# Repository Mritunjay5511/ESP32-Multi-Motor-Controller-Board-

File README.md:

# ESP32-Multi-Motor-Controller-Board-
Custom ESP32-WROOM-32 robotics controller PCB with onboard buck/LDO power regulation, auto-program circuit, and BTS7960/RMCS/relay/servo interfaces. Designed in KiCad.
# ESP32 Dual BTS7960 Motor Driver Breakout Board

A custom 2-layer PCB designed to handle heavy-duty robotics applications. It acts as a central control board breaking out an ESP32 to interface with dual BTS7960 motor drivers, an RMCS driver, and features onboard power regulation.

## Features
- **Microcontroller:** ESP32-WROOM-32
- **Power Stage:** LM2596 Buck Regulator (12v to 5v switching) & AMS1117-3.3 (5v to 3.3v switching)
- **Motor Control Interfaces:** 2x BTS7960 H-Bridge Drivers, 1x RMCS Driver interface
- **Peripherals:** Integrated Micro USB for programming (CH340C), Boot & Reset tactile switches, and broken-out GPIO headers.

## Design Highlights
- Optimized high-frequency switching loops for the buck regulator to minimize EMI.
- Completely isolated RF antenna keepout zone on both layers for maximum wireless signal integrity.
- Solid ground planes on both layers for optimal return paths.

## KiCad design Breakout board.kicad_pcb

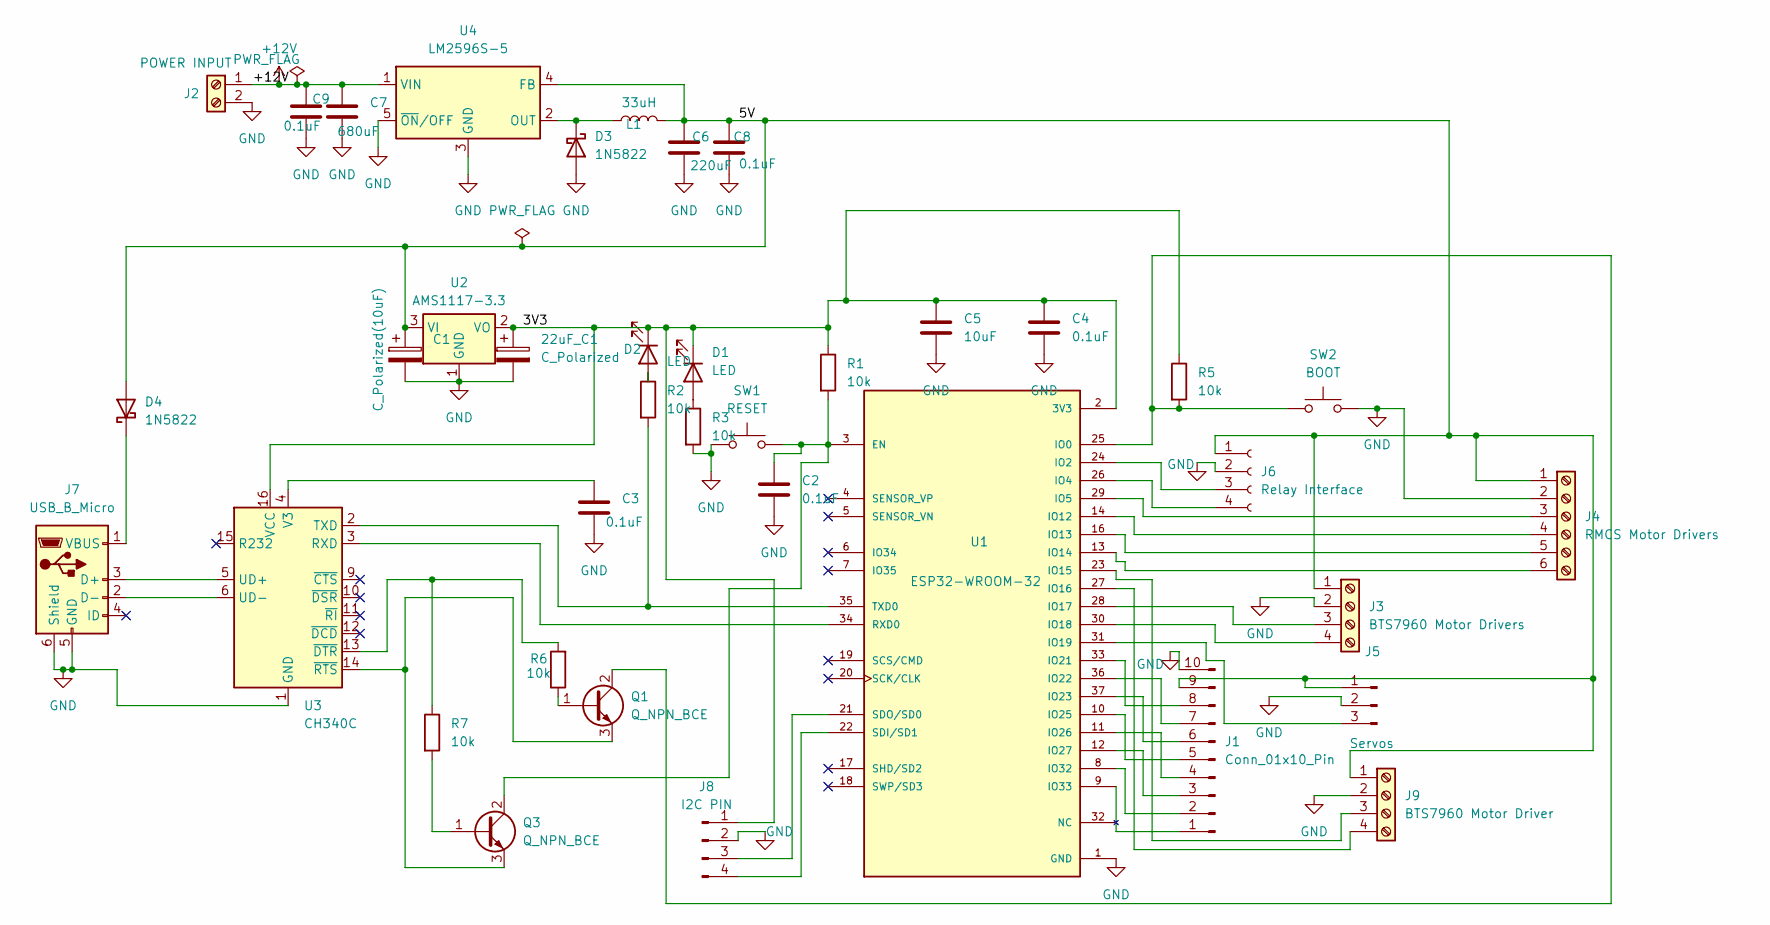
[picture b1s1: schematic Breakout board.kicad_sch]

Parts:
22uF_C1: C_Polarized; CP_Elec_4x5.4
C1: C_Polarized(10uF); CP_Elec_4x5.4
C2, C3, C4, C8, C9: 0.1uF; C_1206_3216Metric
C5: 10uF; C_1206_3216Metric
C6: 220uF; C_1206_3216Metric
C7: 680uF; C_1206_3216Metric
D1, D2: LED; LED_1206_3216Metric
D3: 1N5822; D_DO-201AD_P12.70mm_Horizontal
D4: 1N5822; D_DO-201AD_P15.24mm_Horizontal
J1: Conn_01x10_Pin; PinHeader_1x10_P2.54mm_Vertical
J2: POWER INPUT; TerminalBlock_Phoenix_MKDS-1,5-2-5.08_1x02_P5.08mm_Horizont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
J3: BTS7960 Motor Drivers; TerminalBlock_Phoenix_MKDS-1,5-4-5.08_1x04_P5.08mm_Horizont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
J4: RMCS Motor Drivers; TerminalBlock_Phoenix_MKDS-1,5-6-5.08_1x06_P5.08mm_Horizont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
J5: Servos; PinHeader_1x03_P2.54mm_Vertical
J6: Relay Interface; PinSocket_1x04_P2.54mm_Vertical
J7: USB_B_Micro; USB_Micro-B_Molex-105017-0001
J8: I2C PIN; PinHeader_1x04_P2.54mm_Vertical
J9: BTS7960 Motor Driver; TerminalBlock_Phoenix_MKDS-1,5-4-5.08_1x04_P5.08mm_Horizont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
L1: 33uH; L_1206_3216Metric
Q1, Q3: Q_NPN_BCE; SOT-23
R1, R2, R3, R5, R6, R7: 10k; R_1206_3216Metric
SW1: RESET; SW_PUSH_6mm
SW2: BOOT; SW_PUSH_6mm
U1: ESP32-WROOM-32; MODULE_ESP32-WROOM-32; PARTREV 2.9
U2: AMS1117-3.3; SOT-223-3_TabPin2
U3: CH340C; SOIC-16_3.9x9.9mm_P1.27mm
U4: LM2596S-5; TO-263-5_TabPin3

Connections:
+12V: C7.1, C9.1, J2.1, U4.1 (VIN)
/3V3: 22uF_C1.1, C4.1, C5.1, D1.1 (K), D2.1 (K), J8.1, R1.1, R5.1, U1.2 (3V3), U2.2 (VO), U3.16 (VCC)
/5V: C1.1, C6.1, C8.1, D4.2 (A), J1.9, J3.1, J4.1, J5.1, J6.1, J9.1, L1.2, U2.3 (VI), U4.4 (FB)
GND: 22uF_C1.2, C1.2, C2.2, C3.2, C4.2, C5.2, C6.2, C7.2, C8.2, C9.2, D3.2 (A), J1.10, J2.2, J3.2, J4.2, J5.2, J6.2, J7.5 (GND), J7.6 (Shield), J8.2, J9.2, R3.2, SW1.1, SW2.2, U1.1 (GND), U1.15 (GND), U1.38 (GND), U1.39_1 (GND), U1.39_2 (GND), U1.39_3 (GND), U1.39_4 (GND), U1.39_5 (GND), U1.39_6 (GND), U1.39_7 (GND), U1.39_8 (GND), U1.39_9 (GND), U1.39_10 (GND), U1.39_11 (GND), U1.39_12 (GND), U1.39_13 (GND), U1.39_14 (GND), U1.39_15 (GND), U1.39_16 (GND), U1.39_17 (GND), U1.39_18 (GND), U1.39_19 (GND), U1.39_20 (GND), U1.39_21 (GND), U2.1 (GND), U3.1 (GND), U4.3 (GND), U4.5 (~ON/OFF)
unnamed: D1.2 (A), R3.1
unnamed: D2.2 (A), R2.1
unnamed: D3.1 (K), L1.1, U4.2 (OUT)
unnamed: D4.1 (K), J7.1 (VBUS)
unnamed: J1.1, U1.9 (IO33)
unnamed: J1.2, U1.8 (IO32)
unnamed: J1.3, U1.12 (IO27)
unnamed: J1.4, U1.11 (IO26)
unnamed: J1.5, U1.10 (IO25)
unnamed: J1.6, U1.37 (IO23)
unnamed: J1.7, U1.36 (IO22)
unnamed: J1.8, U1.33 (IO21)
unnamed: J3.3, U1.28 (IO17)
unnamed: J3.4, U1.30 (IO18)
unnamed: J4.3, U1.29 (IO5)
unnamed: J4.4, U1.14 (IO12)
unnamed: J4.5, U1.16 (IO13)
unnamed: J4.6, U1.13 (IO14)
unnamed: J5.3, U1.31 (IO19)
unnamed: J6.3, U1.24 (IO2)
unnamed: J6.4, U1.26 (IO4)
unnamed: J7.3 (D+), U3.5 (UD+)
unnamed: J7.2 (D-), U3.6 (UD-)
unnamed: J8.3, U1.21 (SDO/SD0)
unnamed: J8.4, U1.22 (SDI/SD1)
unnamed: J9.3, U1.23 (IO15)
unnamed: J9.4, U1.27 (IO16)
unnamed: Q1.1 (B), R6.1
unnamed: Q1.2 (C), R5.2, SW2.1, U1.25 (IO0)
unnamed: Q1.3 (E), Q3.3 (E), U3.14 (~RTS)
unnamed: Q3.1 (B), R7.2
unnamed: C2.1, Q3.2 (C), R1.2, SW1.2, U1.3 (EN)
unnamed: U1.34 (RXD0), U3.3 (RXD)
unnamed: R2.2, U1.35 (TXD0), U3.2 (TXD)
unnamed: C3.1, U3.4 (V3)
unnamed: R6.2, R7.1, U3.13 (~DTR)

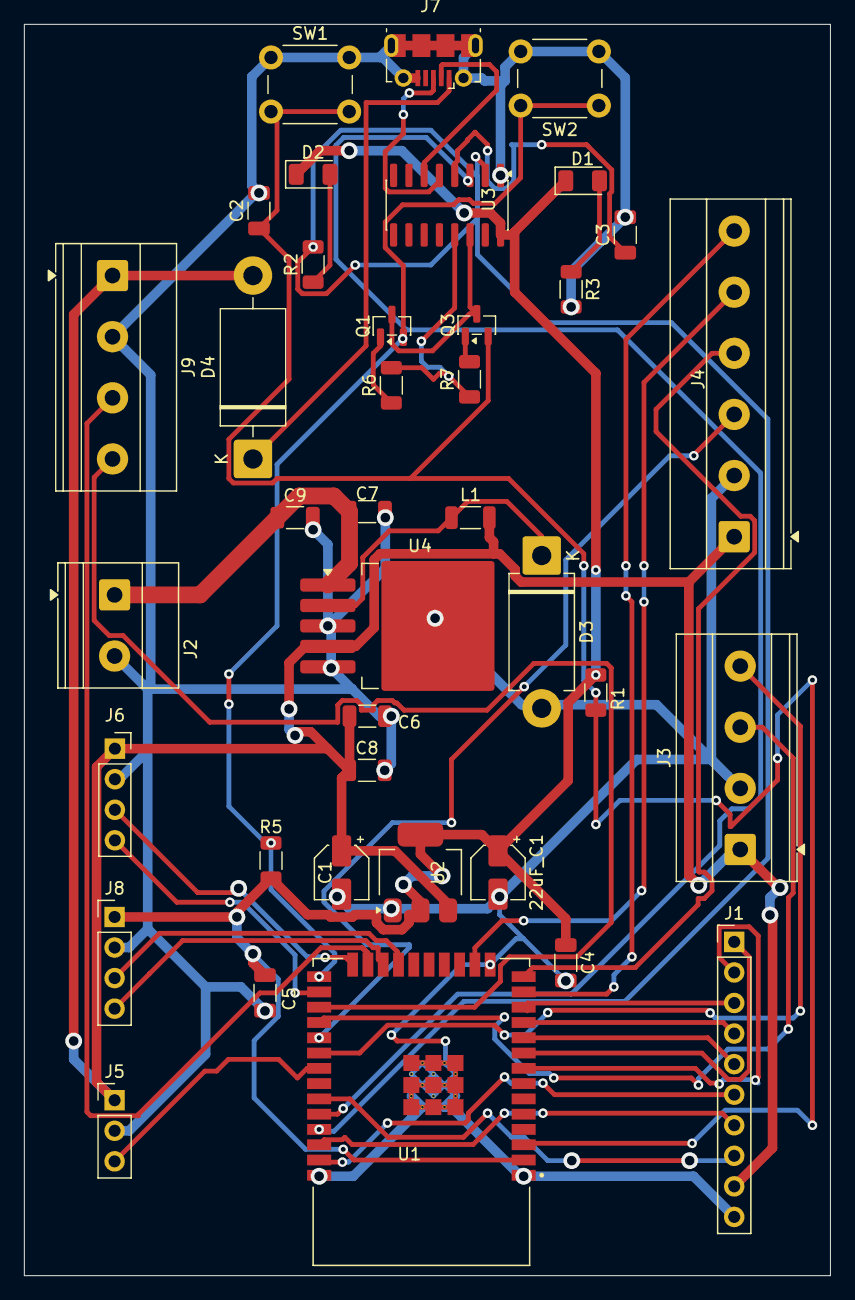
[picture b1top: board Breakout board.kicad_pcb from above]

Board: 2 copper layers, 67.0 x 104.0 mm, 38 parts (0 on the bottom side), 40 nets.

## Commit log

2026-06-23 Initial commit: Added schematic and PCB layout
